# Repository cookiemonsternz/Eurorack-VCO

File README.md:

# VCO

_DIY VCO Eurorack module with saw, triangle, square, and sine output._

#### What?
This is a minimal, hand soldered, sawtooth core VCO module I designed to be inexpensive, fully analog, and with a variety of outputs. To that end, the module features sawtooth, triangle, pwm, and sine outputs, with pwm, fm, and pitch inputs. It internally features temparature tolerant circuitry, as well as having coarse and fine tuning, as well as pitch scale.

#### Why?
DIY eurorack modules are not particularly uncommon, but they often come at the cost of features. A lot of the time such modules lack functionality common to other prebuilt designs, and I wanted to change this. This module has a full standard feature set, including proper PWM and sine outputs.

Also, a lot of eurorack modules are quite bland in terms of design, often lacking any personality and focusing purely on cramming as many knobs in as possible. Here I've taken time to add some (imo) nice art and some extra space on the module.

#### How to use?
This should be pretty self explanatory:
- The pitch knob controls the pitch of the module. If using CV pitch, be sure to set this to the minimum.
- PWM input adjusts the width of the PWM output. The knob to the right of it controls the scale of the PWM CV.
- FM input modulates the frequency by the CV input. The knob controls the FM scale.
- Outputs are along the bottom!
Sawtooth, Triangle, PWM, and Sine, in that order.

#### Tuning
Hopefully, once you've received your pcb and soldered it up, it should look something like this:

Before you properly use it, you'll likely want to tune it.
This can be done by following these instructions:

1. Turn the `pitch` knob on the front of the board to the minimum.
2. Adjust the `coarse` trimpot on the back until the output is roughly A0 (~27.5Hz)
3. Adjust the `fine` trimpot to accurately tune the output.
4. Send 5V into the `1V/OCT` input on the front of the board.
5. Adjust the `scale` trimpot until your output is roughly A4 (~440Hz)
6. Repeat steps 2-5 several times until tuning is accurate at both A0 and A4.

Should the PWM output sound weird, just muck around with the `pwm` trimpot until it sounds normal.
Same thing with the sine or triangle output, just adjust the `tri off` trimpot.

#### Simulations
I've included the simulations I created on LTSpice; VCO contains the full circuit, PWM just the pwm section.

## Renders

## Zine Page

## BOM
_Needed is how many I personally need :)_
| Part                          | Quantity | Needed | Source     | Link                                                  | Lot / Min Amount | Unit  | Net   | Running | Total Incl. Unneeded |
|-------------------------------|----------|--------|------------|-------------------------------------------------------|------------------|-------|-------|---------|----------------------|
| 10n Capacitor                 | 2        | 0      | LCSC       | https://www.lcsc.com/product-detail/C20415578.html    | 10               | $0.59 | NA    | $0.00   | $0.59                |
| 100n Capacitor                | 7        | 0      | LCSC       | https://www.lcsc.com/product-detail/C49002969.html    | 10               | $0.41 | NA    | $0.00   | $1.00                |
| 10u Capacitor                 | 4        | 0      | LCSC       | https://www.lcsc.com/product-detail/C49002971.html    | 5                | $0.81 | NA    | $0.00   | $1.81                |
| 22u Capacitor                 | 1        | 0      | LCSC       | https://www.lcsc.com/product-detail/C18214342.html    | 20               | $0.85 | NA    | $0.00   | $2.66                |
| 100k Resistor                 | 15       | 0      | LCSC       | https://www.lcsc.com/product-detail/C2843019.html     | 100              | $0.82 | NA    | $0.00   | $3.48                |
| 10k Resistor                  | 7        | 0      | LCSC       | https://www.lcsc.com/product-detail/C2903232.html     | 100              | $0.68 | NA    | $0.00   | $4.16                |
| 1k Resistor                   | 6        | 0      | LCSC       | https://www.lcsc.com/product-detail/C2903245.html     | 100              | $0.68 | NA    | $0.00   | $4.84                |
| 1M Resistor                   | 2        | 0      | LCSC       | https://www.lcsc.com/product-detail/C2903250.html     | 100              | $0.79 | NA    | $0.00   | $5.63                |
| 47k Resistor                  | 3        | 0      | LCSC       | https://www.lcsc.com/product-detail/C1364438.html     | 100              | $0.52 | NA    | $0.00   | $6.15                |
| 68k Resistor                  | 1        | 0      | LCSC       | https://www.lcsc.com/product-detail/C1364508.html     | 100              | $0.55 | NA    | $0.00   | $6.70                |
| 14k Resistor                  | 1        | 0      | LCSC       | https://www.lcsc.com/product-detail/C1369251.html     | 100              | $0.87 | NA    | $0.00   | $7.57                |
| 20k Resistor                  | 1        | 0      | LCSC       | https://www.lcsc.com/product-detail/C119353.html      | 50               | $0.57 | NA    | $0.00   | $8.14                |
| 200r Resistor                 | 1        | 0      | LCSC       | https://www.lcsc.com/product-detail/C714576.html      | 20               | $0.68 | NA    | $0.00   | $8.82                |
| 2k Resistor                   | 1        | 0      | LCSC       | https://www.lcsc.com/product-detail/C119330.html      | 50               | $0.52 | NA    | $0.00   | $9.34                |
| 100r Resistor                 | 2        | 0      | LCSC       | https://www.lcsc.com/product-detail/C1366145.html     | 10               | $0.57 | NA    | $0.00   | $9.91                |
| 33r Resistor                  | 2        | 0      | LCSC       | https://www.lcsc.com/product-detail/C713968.html      | 100              | $0.70 | NA    | $0.00   | $10.61               |
| 82r Resistor                  | 2        | 0      | LCSC       | https://www.lcsc.com/product-detail/C119302.html      | 50               | $0.50 | NA    | $0.00   | $11.11               |
| 470r Resistor                 | 1        | 0      | LCSC       | https://www.lcsc.com/product-detail/C129899.html      | 50               | $0.54 | NA    | $0.00   | $11.65               |
| 47r Resistor                  | 2        | 0      | LCSC       | https://www.lcsc.com/product-detail/C119296.html      | 50               | $0.57 | NA    | $0.00   | $12.22               |
| 330r Resistor                 | 1        | 0      | LCSC       | https://www.lcsc.com/product-detail/C713986.html      | 100              | $0.75 | NA    | $0.00   | $12.97               |
| 30r Resistor                  | 2        | 0      | LCSC       | https://www.lcsc.com/product-detail/C18724276.html    | 50               | $0.51 | NA    | $0.00   | $13.48               |
| 120r Resistor                 | 1        | 0      | LCSC       | https://www.lcsc.com/product-detail/C173141.html      | 50               | $1.10 | NA    | $0.00   | $14.58               |
| 39r Resistor                  | 2        | 0      | LCSC       | https://www.lcsc.com/product-detail/C119294.html      | 50               | $0.53 | NA    | $0.00   | $15.11               |
| 6.8k Resistor                 | 1        | 0      | LCSC       | https://www.lcsc.com/product-detail/C3397534.html     | 50               | $0.80 | NA    | $0.00   | $15.91               |
| BC557B                        | 1        | 0      | LCSC       | https://www.lcsc.com/product-detail/C512874.html      | 5                | $0.43 | NA    | $0.00   | $16.34               |
| BC547B                        | 1        | 0      | LCSC       | https://www.lcsc.com/product-detail/C900798.html      | 5                | $0.42 | NA    | $0.00   | $16.76               |
| Diode (1N4148)                | 15       | 15     | LCSC       | https://www.lcsc.com/product-detail/C402212.html      | 50               | $0.47 | $0.47 | $0.47   | $17.23               |
| 3362P 1k Trimpot              | 1        | 1      | LCSC       | https://www.lcsc.com/product-detail/C118947.html      | 5                | $0.72 | $0.72 | $1.19   | $17.95               |
| 3362P 10k Trimpot             | 1        | 1      | LCSC       | https://www.lcsc.com/product-detail/C118956.html      | 5                | $0.82 | $0.82 | $2.01   | $18.77               |
| 3362P 100k Trimpot            | 3        | 3      | LCSC       | https://www.lcsc.com/product-detail/C118966.html      | 5                | $0.77 | $0.77 | $2.78   | $19.54               |
| RK097 1M Vertical Pot         | 1        | 0      | Aliexpress | https://www.aliexpress.com/item/1005007278123055.html | 5                | $1.83 | NA    | $2.78   | $21.37               |
| RK097 100k Vertical Pot       | 2        | 0      | Aliexpress | https://www.aliexpress.com/item/1005007278123055.html | 5                | $1.83 | NA    | $2.78   | $23.20               |
| 10k NTC Thermistor            | 5        | 5      | LCSC       | https://www.lcsc.com/product-detail/C13879.html       | 10               | $0.44 | $0.44 | $3.22   | $23.64               |
| TL074                         | 3        | 3      | LCSC       | https://www.lcsc.com/product-detail/C133542.html      | 1                | $0.69 | $2.08 | $5.30   | $24.33               |
| AMS1117-2.5 SOT223            | 1        | 1      | LCSC       | https://www.lcsc.com/product-detail/C12087.html       | 5                | $0.26 | $1.29 | $6.59   | $24.59               |
| TC7660                        | 1        | 1      | LCSC       | https://www.lcsc.com/product-detail/C640848.html      | 1                | $1.90 | $1.90 | $8.49   | $26.49               |
| PJ301F Audio Jack             | 7        | 7      | Aliexpress | https://www.aliexpress.com/item/1005007344185064.html | 10               | $3.66 | $3.66 | $12.15  | $30.15               |
| 2x8 2.54mm IDC                | 1        | 1      | LCSC       | https://www.lcsc.com/product-detail/C7430313.html     | 5                | $0.08 | $0.42 | $12.57  | $30.23               |
| Aluminium Plate (100x200x2mm) | 1        | 1      | Aliexpress | www.aliexpress.com/item/1005007160296738.html         | 1                | $6.23 | $6.23 | $18.80  | $36.46               |
| M3x18mm Bolt                  | 1        | 0      | Aliexpress | https://www.aliexpress.com/item/32810852732.html      | 50               | $6.43 | NA    | $18.80  | $42.89               |
| M3 Hex Nut                    | 1        | 0      | Aliexpress | https://www.aliexpress.com/item/1005007593861199.html | 50               | $4.89 | NA    | $18.80  | $47.78               |

| Totals                          | Cost   |
|---------------------------------|--------|
| Aliexpress, Inc. Shipping + Tax | $12.67 |
| LCSC, Inc. Shipping + Tax       | $11.83 |
| Totals                          | $24.50 |

## CAD Links
Heres the links to the CAD source, Onshape:
[Panel source](https://cad.onshape.com/documents/2eb193865095ed64e7d8f18f/w/39a8bf3aab3e330703d68c10/e/c0b4bed9abee9891cf892ccc?renderMode=0&uiState=69e5a28fe43246e3fd53c583)

## Directory Structure
- **hardware/**
    - **bom/** - BOM Files (CSV and LibreOffice Calc)
    - **cad/** - CAD Files
        - **render/** - Files for rendering (inc. gltf models)
    - **ltspice/** - LTSpice electrical simulations
    - **vco/** - KiCad files
        - **lib/** - External libraries
        - **production/** - Production files (Gerber, etc.)
- **journals/**
- **zine/** - Zine page :)

## References
Circuit design influenced by:
[Moritz Klein DIY VCO Series](https://www.youtube.com/playlist?list=PLHeL0JWdJLvTuGCyC3qvx0RM39YvopVQN)
[Falstad Diode Clipper](https://www.falstad.com/circuit/e-diodeclip.html)

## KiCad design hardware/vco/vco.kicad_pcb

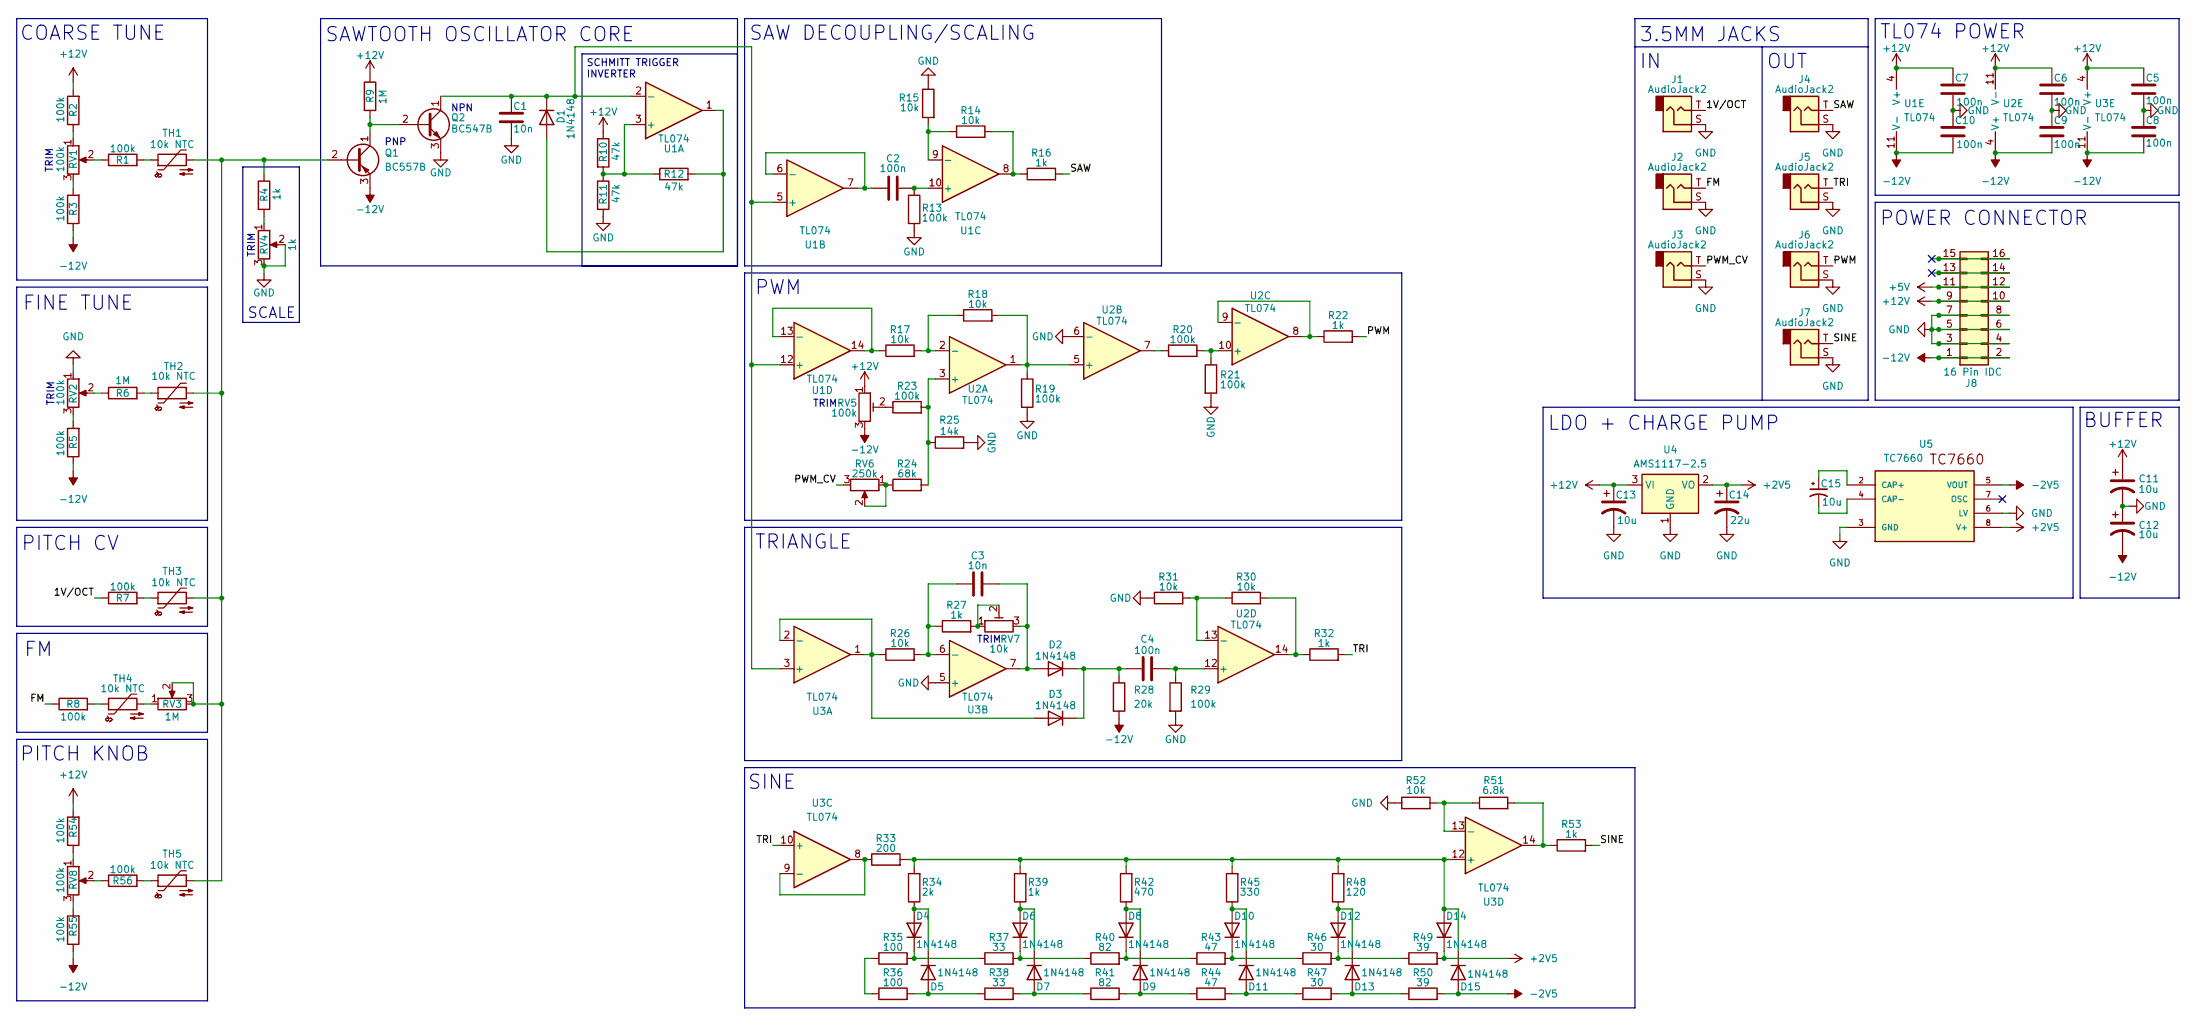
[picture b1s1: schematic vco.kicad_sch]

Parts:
C1, C3: 10n; C_Rect_L9.0mm_W3.3mm_P7.50mm_MKT
C2, C4, C5, C6, C7, C8, C9, C10: 100n; C_Rect_L9.0mm_W4.2mm_P7.50mm_MKT
C11, C12, C13, C15: 10u; CP_Radial_D4.0mm_P2.00mm
C14: 22u; CP_Radial_D4.0mm_P2.00mm
D1, D2, D3, D4, D5, D6, D7, D8, D9, D10, D11, D12, D13, D14, D15: 1N4148; D_DO-35_SOD27_P7.62mm_Horizontal
J1, J2, J3, J4, J5, J6, J7: AudioJack2; Jack_3.5mm_QingPu_WQP-PJ301M-12_Vertical
J8: 16 Pin IDC; IDC-Header_2x08_P2.54mm_Vertical
Q1: BC557B; TO-92_Inline
Q2: BC547B; TO-92_Inline
R1, R2, R3, R5, R7, R8, R13, R19, R20, R21, R23, R29, R54, R55, R56: 100k; R_Axial_DIN0207_L6.3mm_D2.5mm_P2.54mm_Vertical
R4, R16, R22, R27, R32, R39, R53: 1k; R_Axial_DIN0207_L6.3mm_D2.5mm_P2.54mm_Vertical
R6, R9: 1M; R_Axial_DIN0207_L6.3mm_D2.5mm_P2.54mm_Vertical
R10, R11, R12: 47k; R_Axial_DIN0207_L6.3mm_D2.5mm_P2.54mm_Vertical
R14, R15, R17, R18, R26, R30, R31, R52: 10k; R_Axial_DIN0207_L6.3mm_D2.5mm_P2.54mm_Vertical
R24: 68k; R_Axial_DIN0207_L6.3mm_D2.5mm_P2.54mm_Vertical
R25: 14k; R_Axial_DIN0207_L6.3mm_D2.5mm_P2.54mm_Vertical
R28: 20k; R_Axial_DIN0207_L6.3mm_D2.5mm_P2.54mm_Vertical
R33: 200; R_Axial_DIN0207_L6.3mm_D2.5mm_P2.54mm_Vertical
R34: 2k; R_Axial_DIN0207_L6.3mm_D2.5mm_P2.54mm_Vertical
R35, R36: 100; R_Axial_DIN0207_L6.3mm_D2.5mm_P2.54mm_Vertical
R37, R38: 33; R_Axial_DIN0207_L6.3mm_D2.5mm_P2.54mm_Vertical
R40, R41: 82; R_Axial_DIN0207_L6.3mm_D2.5mm_P2.54mm_Vertical
R42: 470; R_Axial_DIN0207_L6.3mm_D2.5mm_P2.54mm_Vertical
R43, R44: 47; R_Axial_DIN0207_L6.3mm_D2.5mm_P2.54mm_Vertical
R45: 330; R_Axial_DIN0207_L6.3mm_D2.5mm_P2.54mm_Vertical
R46, R47: 30; R_Axial_DIN0207_L6.3mm_D2.5mm_P2.54mm_Vertical
R48: 120; R_Axial_DIN0207_L6.3mm_D2.5mm_P2.54mm_Vertical
R49, R50: 39; R_Axial_DIN0207_L6.3mm_D2.5mm_P2.54mm_Vertical
R51: 6.8k; R_Axial_DIN0207_L6.3mm_D2.5mm_P2.54mm_Vertical
RV1, RV2, RV5: 100k; TRIM_3362P-1-253LF
RV3: 1M; Potentiometer_Alps_RK09L_Single_Vertical
RV4: 1k; TRIM_3362P-1-253LF
RV6: 250k; Potentiometer_Alps_RK09L_Single_Vertical
RV7: 10k; TRIM_3362P-1-253LF
RV8: 100k; Potentiometer_Alps_RK09L_Single_Vertical
TH1, TH2, TH3, TH4, TH5: 10k NTC; R_Axial_DIN0204_L3.6mm_D1.6mm_P1.90mm_Vertical
U1, U2, U3: TL074; DIP-14_W7.62mm
U4: AMS1117-2.5; SOT-223-3_TabPin2
U5: TC7660; DIL08

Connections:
+2V5: C14.1, D14.1 (K), R49.2, U4.2 (VO), U5.8 (V+)
+5V: J8.11, J8.12
+12V: C5.1, C6.1, C7.1, C11.1, C13.1, J8.9, J8.10, R2.2, R9.1, R10.1, R54.2, RV5.1, U1.4 (V+), U2.11 (V-), U3.4 (V+), U4.3 (VI)
-2V5: D15.2 (A), R50.2, U5.5 (VOUT)
-12V: C8.2, C9.2, C10.2, C12.2, J8.1, J8.2, Q1.3 (E), R3.1, R5.1, R28.2, R55.1, RV5.3, U1.11 (V-), U2.4 (V+), U3.11 (V-)
/1V/OCT: J1.T, R7.1
/FM: J2.T, R8.1
/PWM: J6.T, R22.2
/PWM_CV: J3.T, RV6.3
/SAW: J4.T, R16.2
/SINE: J7.T, R53.2
/TRI: J5.T, R32.2, U3.10 (+)
GND: C1.2, C5.2, C6.2, C7.2, C8.1, C9.1, C10.1, C11.2, C12.1, C13.2, C14.2, J1.S, J2.S, J3.S, J4.S, J5.S, J6.S, J7.S, J8.3, J8.4, J8.5, J8.6, J8.7, J8.8, Q2.3 (E), R11.2, R13.2, R15.1, R19.2, R21.2, R25.2, R29.2, R31.1, R52.1, RV2.1, RV4.2, RV4.3, U2.6 (-), U3.5 (+), U4.1 (GND), U5.3 (GND), U5.6 (LV)
unnamed: D1.2 (A), R12.2, U1.1
unnamed: C1.1, D1.1 (K), Q2.1 (C), U1.2 (-), U1.5 (+), U1.12 (+), U3.3 (+)
unnamed: C3.2, D2.2 (A), RV7.3, U3.7
unnamed: C4.1, D2.1 (K), D3.1 (K), R28.1
unnamed: D3.2 (A), R26.1, U3.1, U3.2 (-)
unnamed: D4.2 (A), D5.1 (K), R34.1
unnamed: D4.1 (K), R35.2, R37.1
unnamed: D5.2 (A), R36.2, R38.1
unnamed: D6.2 (A), D7.1 (K), R39.1
unnamed: D6.1 (K), R37.2, R40.1
unnamed: D7.2 (A), R38.2, R41.1
unnamed: D8.2 (A), D9.1 (K), R42.1
unnamed: D8.1 (K), R40.2, R43.1
unnamed: D9.2 (A), R41.2, R44.1
unnamed: D10.2 (A), D11.1 (K), R45.1
unnamed: D10.1 (K), R43.2, R46.1
unnamed: D11.2 (A), R44.2, R47.1
unnamed: D12.2 (A), D13.1 (K), R48.1
unnamed: D12.1 (K), R46.2, R49.1
unnamed: D13.2 (A), R47.2, R50.1
unnamed: D14.2 (A), D15.1 (K), R33.2, R34.2, R39.2, R42.2, R45.2, R48.2, U3.12 (+)
unnamed: Q1.2 (B), R4.1, RV3.2, RV3.3, TH1.2, TH2.2, TH3.2, TH5.2
unnamed: Q1.1 (C), Q2.2 (B), R9.2
unnamed: R1.1, RV1.2
unnamed: R1.2, TH1.1
unnamed: R2.1, RV1.1
unnamed: R3.2, RV1.3
unnamed: R4.2, RV4.1
unnamed: R5.2, RV2.3
unnamed: R6.1, RV2.2
unnamed: R6.2, TH2.1
unnamed: R7.2, TH3.1
unnamed: R8.2, TH4.1
unnamed: R14.2, R16.1, U1.8
unnamed: R20.1, U2.7
unnamed: R23.1, RV5.2
unnamed: R24.1, RV6.1, RV6.2
unnamed: R27.2, RV7.1, RV7.2
unnamed: R30.2, R32.1, U2.14
unnamed: R35.1, R36.1
unnamed: R51.2, R53.1, U3.14
unnamed: R54.1, RV8.1
unnamed: R55.2, RV8.3
unnamed: R56.1, RV8.2
unnamed: R56.2, TH5.1
unnamed: RV3.1, TH4.2
unnamed: R10.2, R11.1, R12.1, U1.3 (+)
unnamed: C2.1, U1.6 (-), U1.7
unnamed: C2.2, R13.1, U1.10 (+)
unnamed: R14.1, R15.2, U1.9 (-)
unnamed: R17.1, U1.13 (-), U1.14
unnamed: R23.2, R24.2, R25.1, U2.3 (+)
unnamed: R17.2, R18.1, U2.2 (-)
unnamed: R18.2, R19.1, U2.1, U2.5 (+)
unnamed: R20.2, R21.1, U2.10 (+)
unnamed: R22.1, U2.8, U2.9 (-)
unnamed: C4.2, R29.1, U2.12 (+)
unnamed: R30.1, R31.2, U2.13 (-)
unnamed: C3.1, R26.2, R27.1, U3.6 (-)
unnamed: R33.1, U3.8, U3.9 (-)
unnamed: R51.1, R52.2, U3.13 (-)
unnamed: C15.1, U5.2 (CAP+)
unnamed: C15.2, U5.4 (CAP-)

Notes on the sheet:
TL074 POWER
NPN
SCALE
PITCH KNOB
FINE TUNE
COARSE TUNE
SINE
PNP
BUFFER
SCHMITT TRIGGER INVERTER
LDO + CHARGE PUMP
OUT
TRIM
3.5MM JACKS
TRIANGLE
PWM
SAWTOOTH OSCILLATOR CORE
SAW DECOUPLING/SCALING
POWER CONNECTOR
PITCH CV

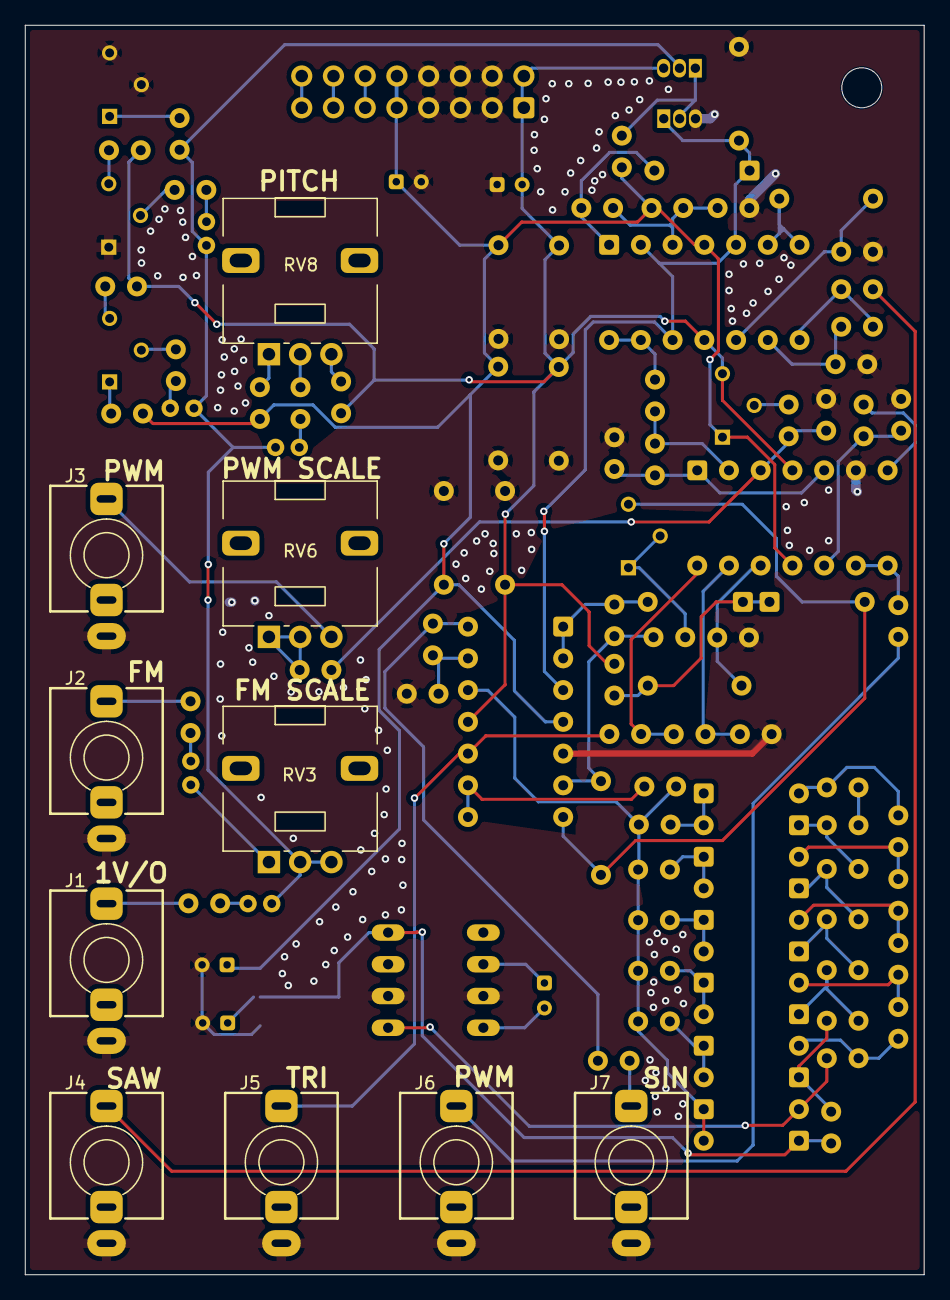
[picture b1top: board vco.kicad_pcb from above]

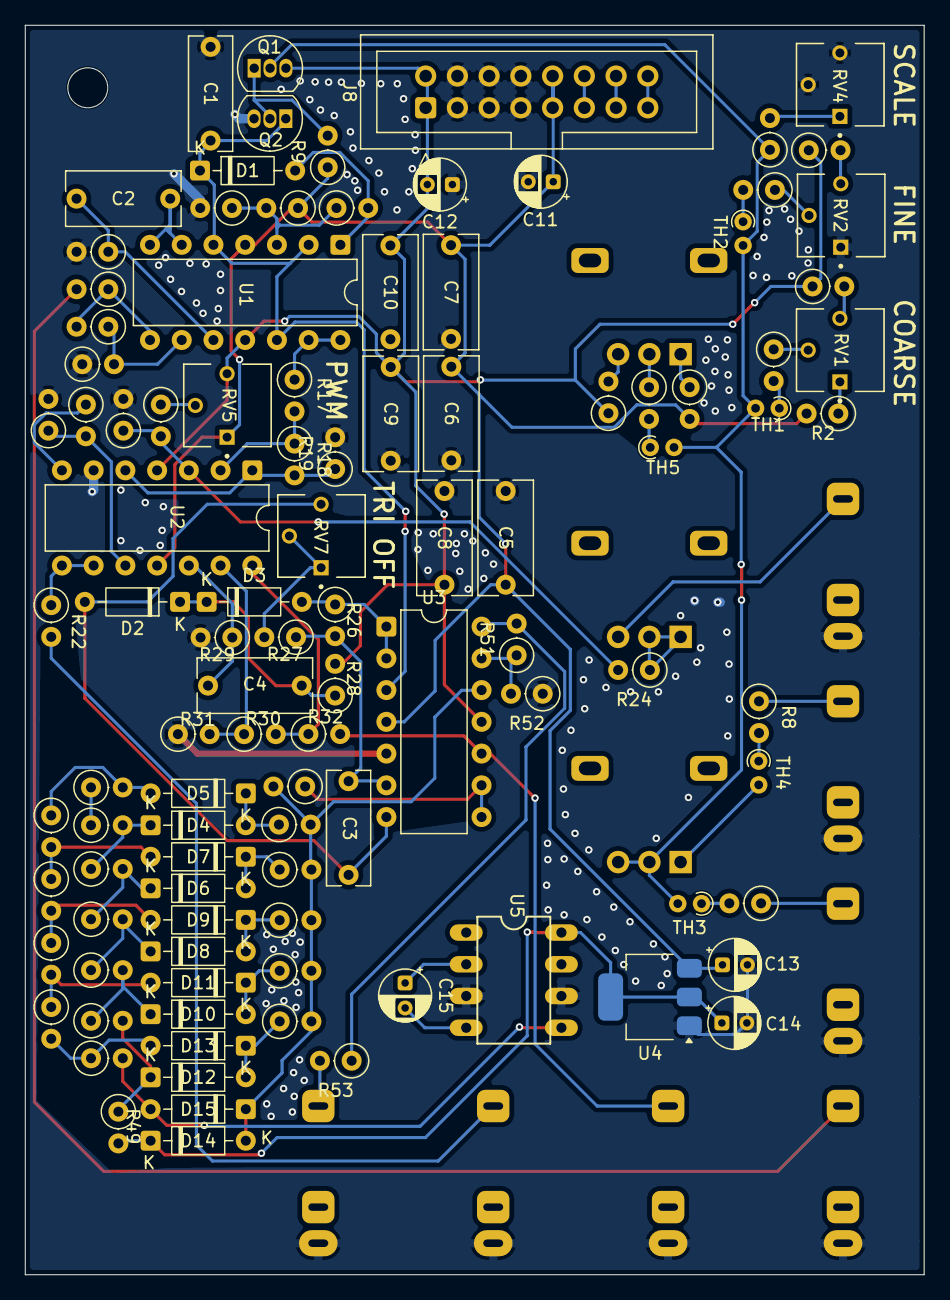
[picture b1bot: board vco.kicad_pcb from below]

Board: 2 copper layers, 71.9 x 100.0 mm, 114 parts (104 on the bottom side), 76 nets.

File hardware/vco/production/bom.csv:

Designator,Footprint,Quantity,Value,LCSC Part #
"C1, C3",C_Rect_L9.0mm_W3.3mm_P7.50mm_MKT,2,10n,
"C10, C2, C4, C5, C6, C7, C8, C9",C_Rect_L9.0mm_W4.2mm_P7.50mm_MKT,8,100n,
"C11, C12, C13, C15",CP_Radial_D4.0mm_P2.00mm,4,10u,
C14,CP_Radial_D4.0mm_P2.00mm,1,22u,
"D1, D10, D11, D12, D13, D14, D15, D2, D3, D4, D5, D6, D7, D8, D9",D_DO-35_SOD27_P7.62mm_Horizontal,15,1N4148,
"J1, J2, J3, J4, J5, J6, J7",Jack_3.5mm_QingPu_WQP-PJ301M-12_Vertical,7,AudioJack2,
J8,IDC-Header_2x08_P2.54mm_Vertical,1,16 Pin IDC,
Q1,TO-92_Inline,1,BC557B,
Q2,TO-92_Inline,1,BC547B,
"R1, R13, R19, R2, R20, R21, R23, R29, R3, R5, R54, R55, R56, R7, R8",R_Axial_DIN0207_L6.3mm_D2.5mm_P2.54mm_Vertical,15,100k,
"R10, R11, R12",R_Axial_DIN0207_L6.3mm_D2.5mm_P2.54mm_Vertical,3,47k,
"R14, R15, R17, R18, R26, R30, R31, R52",R_Axial_DIN0207_L6.3mm_D2.5mm_P2.54mm_Vertical,8,10k,
"R16, R22, R27, R32, R39, R4, R53",R_Axial_DIN0207_L6.3mm_D2.5mm_P2.54mm_Vertical,7,1k,
R24,R_Axial_DIN0207_L6.3mm_D2.5mm_P2.54mm_Vertical,1,68k,
R25,R_Axial_DIN0207_L6.3mm_D2.5mm_P2.54mm_Vertical,1,14k,
R28,R_Axial_DIN0207_L6.3mm_D2.5mm_P2.54mm_Vertical,1,20k,
R33,R_Axial_DIN0207_L6.3mm_D2.5mm_P2.54mm_Vertical,1,200,
R34,R_Axial_DIN0207_L6.3mm_D2.5mm_P2.54mm_Vertical,1,2k,
"R35, R36",R_Axial_DIN0207_L6.3mm_D2.5mm_P2.54mm_Vertical,2,100,
"R37, R38",R_Axial_DIN0207_L6.3mm_D2.5mm_P2.54mm_Vertical,2,33,
"R40, R41",R_Axial_DIN0207_L6.3mm_D2.5mm_P2.54mm_Vertical,2,82,
R42,R_Axial_DIN0207_L6.3mm_D2.5mm_P2.54mm_Vertical,1,470,
"R43, R44",R_Axial_DIN0207_L6.3mm_D2.5mm_P2.54mm_Vertical,2,47,
R45,R_Axial_DIN0207_L6.3mm_D2.5mm_P2.54mm_Vertical,1,330,
"R46, R47",R_Axial_DIN0207_L6.3mm_D2.5mm_P2.54mm_Vertical,2,30,
R48,R_Axial_DIN0207_L6.3mm_D2.5mm_P2.54mm_Vertical,1,120,
"R49, R50",R_Axial_DIN0207_L6.3mm_D2.5mm_P2.54mm_Vertical,2,39,
R51,R_Axial_DIN0207_L6.3mm_D2.5mm_P2.54mm_Vertical,1,6.8k,
"R6, R9",R_Axial_DIN0207_L6.3mm_D2.5mm_P2.54mm_Vertical,2,1M,
"RV1, RV2, RV5",TRIM_3362P-1-253LF,3,100k,
RV3,Potentiometer_Alps_RK09L_Single_Vertical,1,1M,
RV4,TRIM_3362P-1-253LF,1,1k,
RV6,Potentiometer_Alps_RK09L_Single_Vertical,1,250k,
RV7,TRIM_3362P-1-253LF,1,10k,
RV8,Potentiometer_Alps_RK09L_Single_Vertical,1,100k,
"TH1, TH2, TH3, TH4, TH5",R_Axial_DIN0204_L3.6mm_D1.6mm_P1.90mm_Vertical,5,10k NTC,
"U1, U2, U3",DIP-14_W7.62mm,3,TL074,
U4,SOT-223-3_TabPin2,1,AMS1117-2.5,
U5,DIL08,1,TC7660,

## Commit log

2026-04-16 Init commit
2026-04-18 finish circuit
2026-04-18 Start kicad schematic
2026-04-18 start of tht version
2026-04-18 end of first layout att
2026-04-20 Polish for submission
2026-04-20 add zine to readme directory
2026-04-20 lockfiles + autosaves crap
2026-04-20 fix image paths
2026-04-25 add cad full assembly
2026-04-28 update bom
